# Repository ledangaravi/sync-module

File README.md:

# sync-module
Synchronisation Module for the NGNI Spike Sorting Platform

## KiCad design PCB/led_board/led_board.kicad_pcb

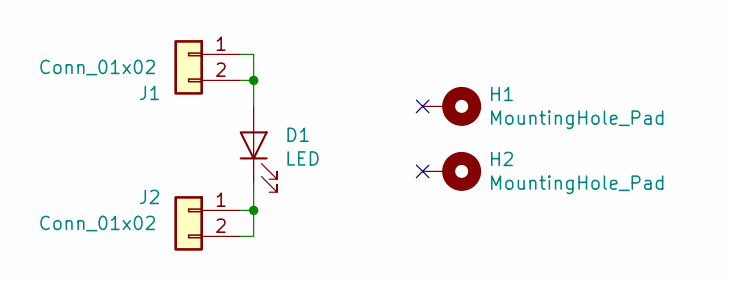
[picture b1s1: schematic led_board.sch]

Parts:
D1: LED; SFH4726AS
H1, H2: MountingHole_Pad; MountingHole_2.7mm_M2.5_Pad
J1, J2: Conn_01x02; SolderWirePad_1x02_P3.81mm_Drill1.2mm

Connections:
unnamed: D1.1 (K), J2.1, J2.2
unnamed: D1.2 (A), J1.1, J1.2

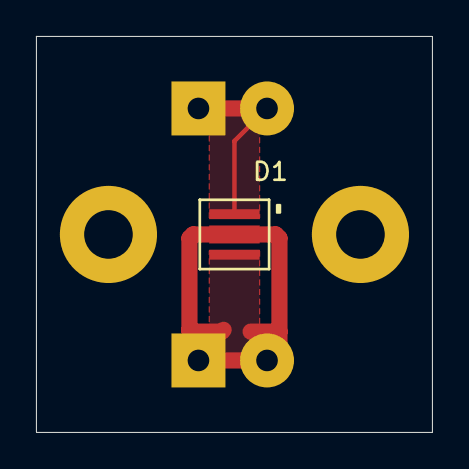
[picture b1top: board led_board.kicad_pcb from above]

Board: 2 copper layers, 22.0 x 22.0 mm, 5 parts (0 on the bottom side), 2 nets.

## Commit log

2020-07-05 add Testing and CV
